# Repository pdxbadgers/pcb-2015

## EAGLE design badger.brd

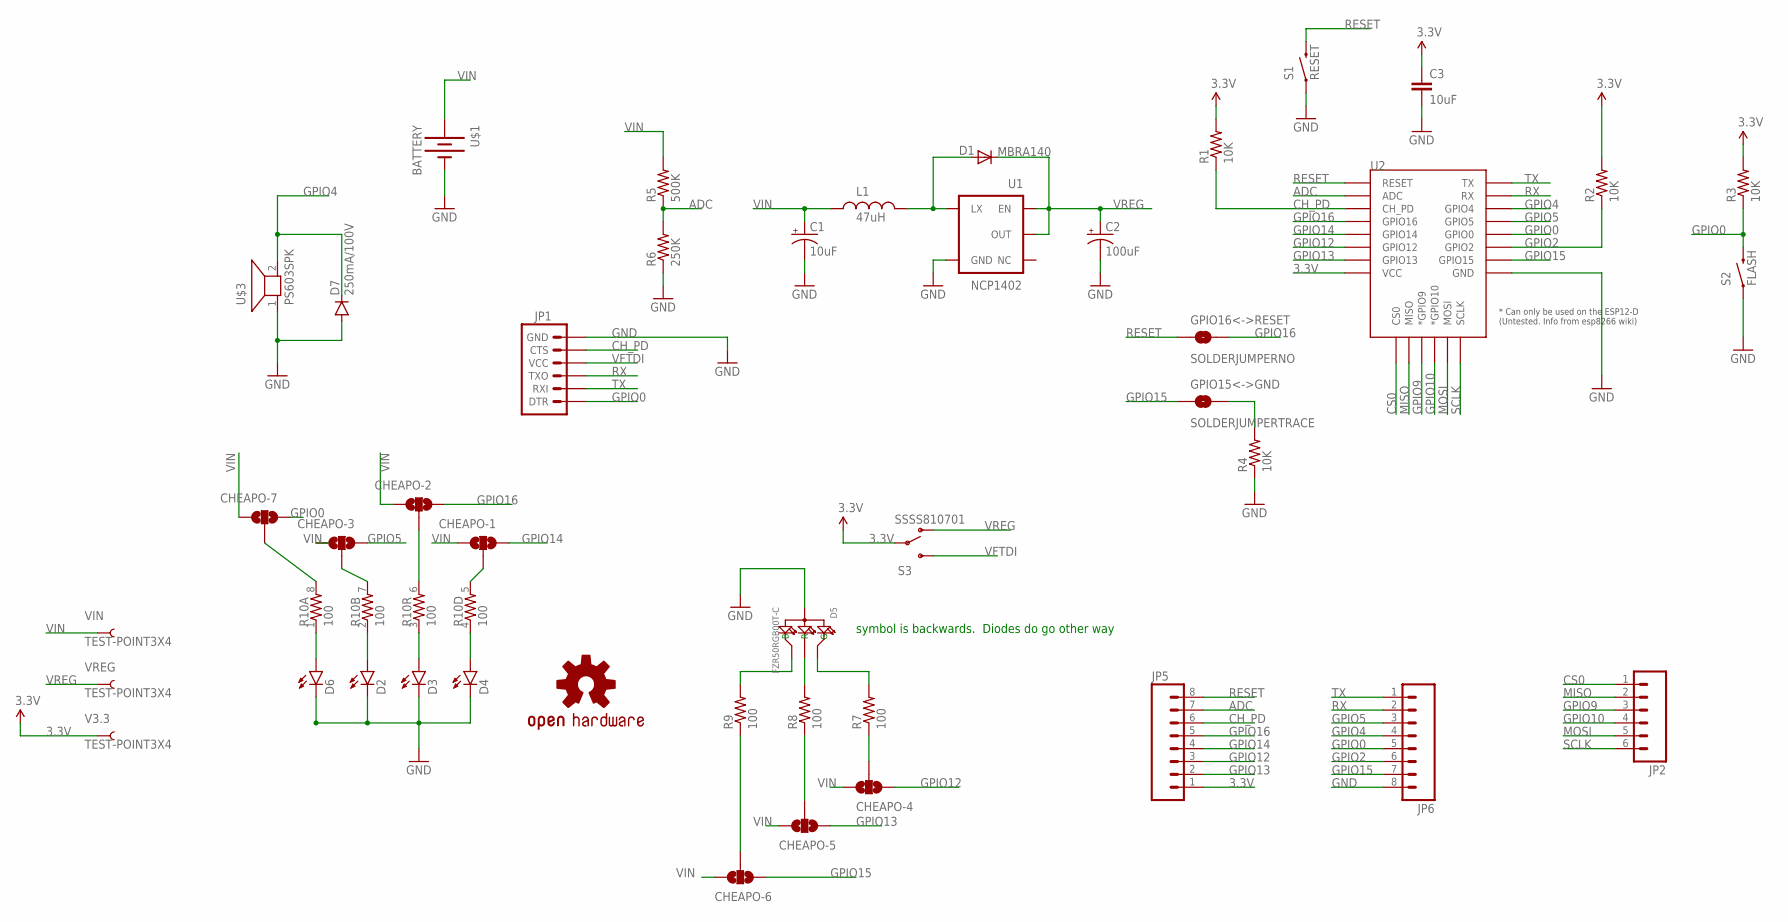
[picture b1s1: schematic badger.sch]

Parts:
C1: 10uF; EIA3216
C2: 100uF; EIA3528
C3: 10uF; 0603-CAP
CHEAPO-1, CHEAPO-2, CHEAPO-3, CHEAPO-4, CHEAPO-5, CHEAPO-6, CHEAPO-7: SOLDERJUMPER_2WAYT; SJ_2
D1: MBRA140; SMA-DIODE
D2, D3, D4, D6: LED-3MM-NO_SILK; LED3MM-NS
D5: FZR50RGB00T-C; LED4-1.3-D5.0MM
D7: 250mA/100V; SOD-323
GPIO15<->GND: SOLDERJUMPERTRACE; SJ_2S-TRACE
GPIO16<->RESET: SOLDERJUMPERNO; SJ_2S-NO
JP1: ARDUINO_SERIAL_PROGRAMLOCK; 1X06_LOCK
JP2: M06LOCK; 1X06_LOCK
JP5, JP6: M08LOCK; 1X08_LOCK
L1: 47uH; CR54
LOGO1: OSHW-LOGOL-COPPER; OSHW-LOGO-L_COPPER
R1, R2, R3, R4: 10K; 0603-RES
R5: 500K; 0603-RES
R6: 250K; 0603-RES
R7, R8, R9: 100; 1206
R10: 100; 0603-ARV
S1: RESET; TACTILE-SWITCH-SMD
S2: FLASH; TACTILE-SWITCH-SMD
S3: SSSS810701; SSSS8
U1: NCP1402; SOT23-5
U2: ESP12ESMD; ESP12E-SMD
U$1: BATTERY; HOLDER
U$3: PS603SPK; PS603
V3.3: TEST-POINT3X4; PAD.03X.04
VIN: TEST-POINT3X4; PAD.03X.04
VREG: TEST-POINT3X4; PAD.03X.04

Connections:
3.3V: C3.1, JP5.1, R1.2, R2.2, R3.2, S3.P$2, U2.VCC, V3.3.P$1
ADC: JP5.7, R5.1, R6.2, U2.ADC
CH_PD: JP1.5 (CTS), JP5.6, R1.1, U2.CH_PD
CS0: JP2.1, U2.CS0
GND: C1.C (-), C2.C (-), C3.2, D2.K (C), D3.K (C), D4.K (C), D5.C (+), D6.K (C), D7.A, JP1.6 (GND), JP6.8, R4.1, R6.1, S1.1, S2.1, U1.4 (GND), U2.GND, U$1.P$2 (-), U$3.1
GPIO0: CHEAPO-7.3, JP1.1 (DTR), JP6.5, R3.1, S2.3 (2), U2.GPIO0
GPIO2: JP6.6, R2.1, U2.GPIO2
GPIO4: D7.C, JP6.4, U2.GPIO4, U$3.2
GPIO5: CHEAPO-3.3, JP6.3, U2.GPIO5
GPIO9: JP2.3, U2.GPIO9 (*GPIO9)
GPIO10: JP2.4, U2.GPIO10 (*GPIO10)
GPIO12: CHEAPO-4.1, JP5.3, U2.GPIO12
GPIO13: CHEAPO-5.1, JP5.2, U2.GPIO13
GPIO14: CHEAPO-1.3, JP5.4, U2.GPIO14
GPIO15: CHEAPO-6.1, GPIO15<->GND.1, JP6.7, U2.GPIO15
GPIO16: CHEAPO-2.3, GPIO16<->RESET.2, JP5.5, U2.GPIO16
MISO: JP2.2, U2.MISO
MOSI: JP2.5, U2.MOSI
unnamed: GPIO15<->GND.2, R4.2
unnamed: D5.R, R8.2
unnamed: D1.A, L1.P$2 (2), U1.5 (LX)
unnamed: D5.G, R7.2
unnamed: D2.A, R10.2 (1)
unnamed: D3.A, R10.3 (1)
unnamed: D4.A, R10.4 (1)
unnamed: D5.B, R9.2
unnamed: CHEAPO-4.2, R7.1
unnamed: D6.A, R10.1
unnamed: CHEAPO-5.2, R8.1
unnamed: CHEAPO-3.2, R10.7 (2)
unnamed: CHEAPO-2.2, R10.6 (2)
unnamed: CHEAPO-1.2, R10.5 (2)
unnamed: CHEAPO-7.2, R10.8 (2)
unnamed: CHEAPO-6.2, R9.1
RESET: GPIO16<->RESET.1, JP5.8, S1.3 (2), U2.RESET
RX: JP1.3 (TXO), JP6.2, U2.RXD0 (RX)
SCLK: JP2.6, U2.SCLK
TX: JP1.2 (RXI), JP6.1, U2.TXD0 (TX)
VFTDI: JP1.4 (VCC), S3.P$1 (S)
VIN: C1.A (+), CHEAPO-1.1, CHEAPO-2.1, CHEAPO-3.1, CHEAPO-4.3, CHEAPO-5.3, CHEAPO-6.3, CHEAPO-7.1, L1.P$1 (1), R5.2, U$1.P$1 (+), VIN.P$1
VREG: C2.A (+), D1.C, S3.P$3 (O), U1.1 (EN), U1.2 (OUT), VREG.P$1

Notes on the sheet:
symbol is backwards. Diodes do go other way

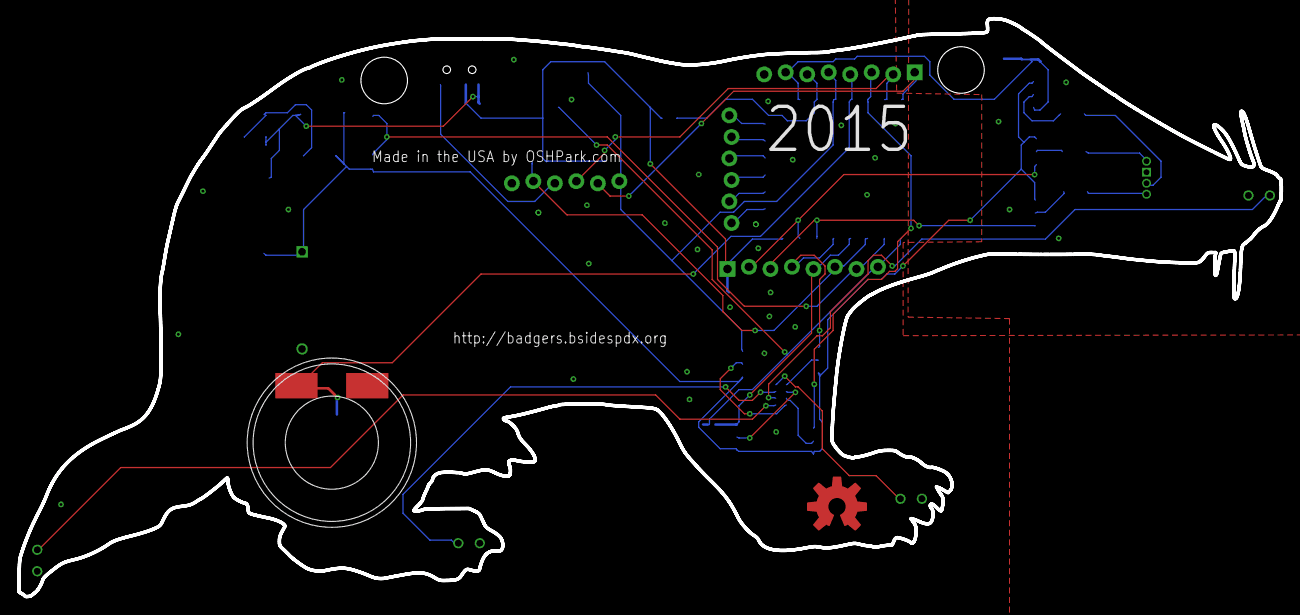
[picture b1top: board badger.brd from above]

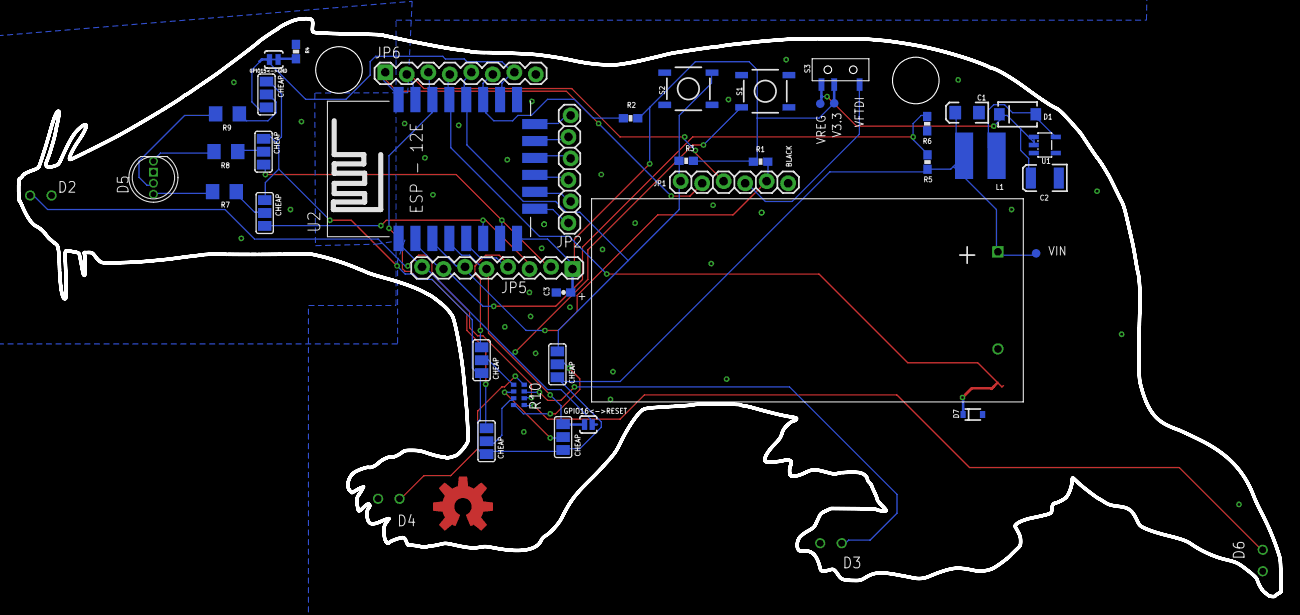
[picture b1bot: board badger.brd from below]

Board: 2 copper layers, 149.2 x 68.3 mm, 45 parts (43 on the bottom side), 41 nets.

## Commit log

2015-09-03 initial checkin
2015-09-04 add eagle files
2015-09-04 add esp8266 lib and add part
2015-09-08 more updates
2015-09-16 some updates
2015-09-19 add switch and associated scripting
2015-09-22 updates to schematic
2015-09-22 outline, but hit the limits of eagle free
2015-09-22 initial placing
2015-09-22 prior to route
2015-09-23 as sent to itead
2015-09-23 Fix #1
    Thanks to briand!
2015-09-23 make the gnd planes connect a little better on the head
2015-09-24 Fix #3
    All headers now locking
2015-09-24 as sent to oshpark for proto
2015-09-28 fix #8
2015-09-28 fix #7
2015-10-01 Add 5mil dimension buffer; bring vias closer in; reroute
2015-10-01 unrouted fixes
    speaker/pin collision
    add source bitmaps to repo
    bsides logo now hi-res
    oshpark logo
    harmonize (mostly) silk placement and size
2015-10-01 routed
2015-10-01 Add polorization mark for C3
2015-10-01 move silk label out out from under speaker
2015-10-01 more groundier
2015-10-01 Take joe fitz's cam.. modify
2015-10-01 Add a set of test gerbers to see if cam job is right
2015-10-02 year; r4; url move; button font
2015-10-02 tidy up
2015-10-02 final(?) design? - rerouted - rgb led now with common gnd - rgb led now powered by vin with cheapo varient - new cam
2015-10-02 fixup cam test
2015-10-02 maybe a more robust gndplane. But unsure about clearence
2015-10-02 adding oshpark dru
2015-10-02 reapply design rules; dimension/pour 6mil; gnd
    added gnd trace near antenna in case of mill problems
2015-10-04 Another test-spin
2015-10-04 Now without the trestrict
2015-10-04 reconnect diode; via cleanups
    Noticed that stapling vias were octogon and larger drill diameter. Fixed
2015-10-04 from proposed to sent-out

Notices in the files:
parts and their libraries:
SparkFun-Resistors: Licensing: Creative Commons ShareAlike 4.0 International - https://creativecommons.org/licenses/by-sa/4.0
